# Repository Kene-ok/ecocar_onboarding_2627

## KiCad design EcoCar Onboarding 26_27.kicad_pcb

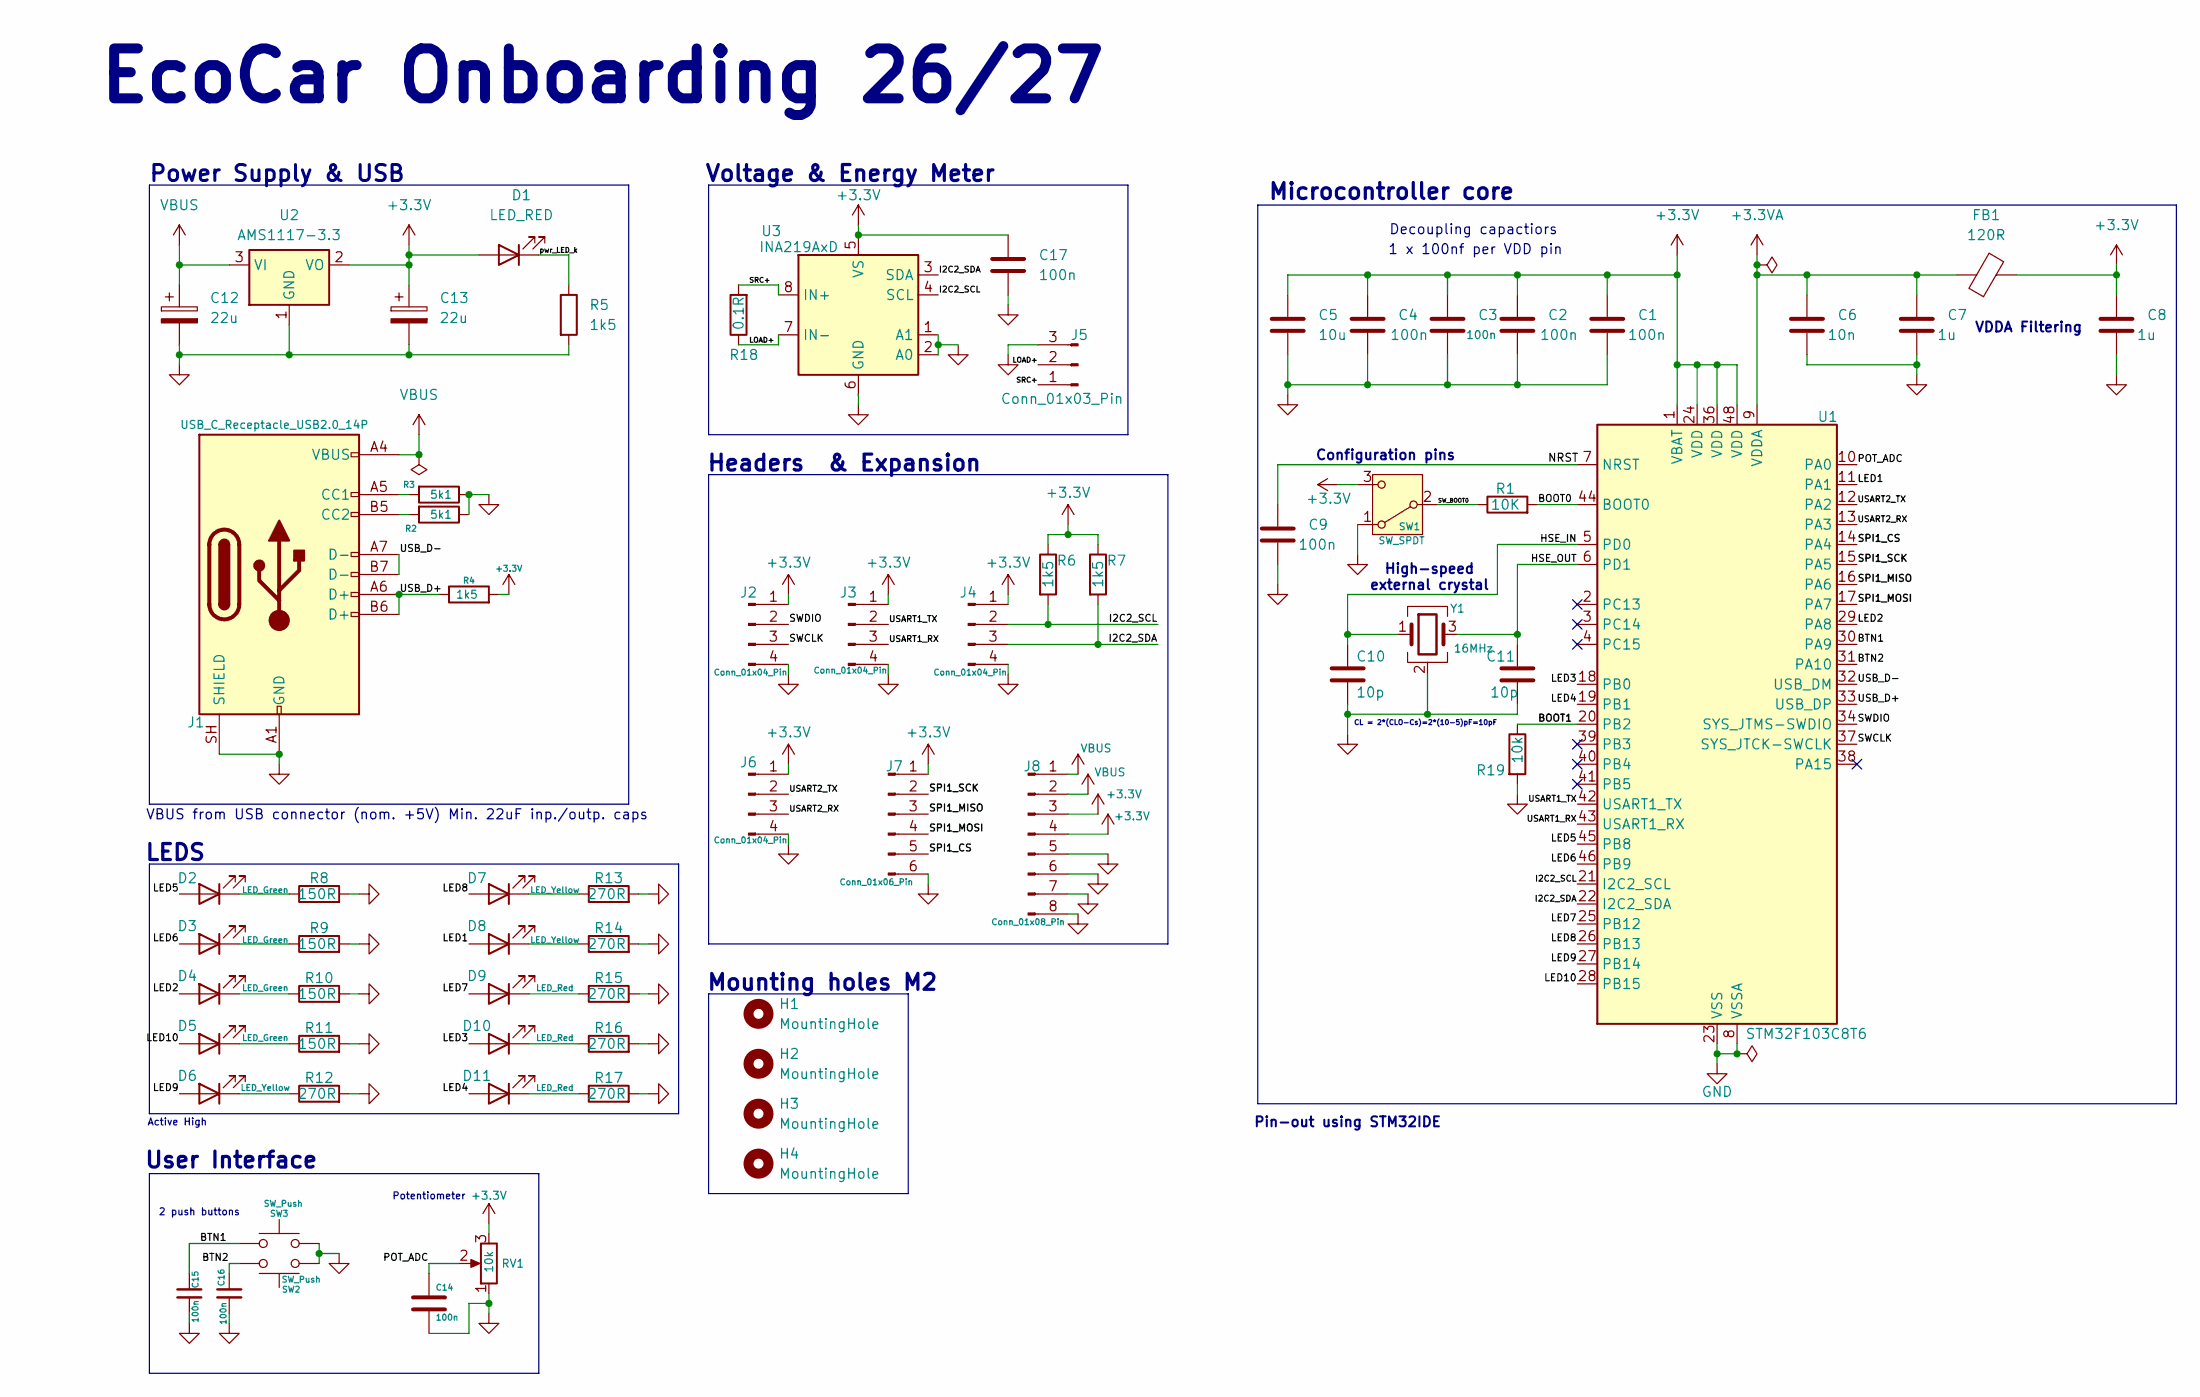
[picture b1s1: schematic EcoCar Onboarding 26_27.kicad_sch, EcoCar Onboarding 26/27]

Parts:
C1, C2, C3, C4, C9, C14, C15, C16, C17: 100n; C_0603_1608Metric_Pad1.08x0.95mm_HandSolder
C5: 10u; C_0603_1608Metric_Pad1.08x0.95mm_HandSolder
C6: 10n; C_0603_1608Metric_Pad1.08x0.95mm_HandSolder
C7, C8: 1u; C_0603_1608Metric_Pad1.08x0.95mm_HandSolder
C10, C11: 10p; C_0603_1608Metric_Pad1.08x0.95mm_HandSolder
C12, C13: 22u; CP_EIA-3216-18_Kemet-A
D1: LED_RED; LED_0603_1608Metric_Pad1.05x0.95mm_HandSolder
D2, D3, D4, D5: LED_Green; LED_0603_1608Metric_Pad1.05x0.95mm_HandSolder
D6, D7, D8: LED_Yellow; LED_0603_1608Metric_Pad1.05x0.95mm_HandSolder
D9, D10, D11: LED_Red; LED_0603_1608Metric_Pad1.05x0.95mm_HandSolder
FB1: 120R; L_0603_1608Metric_Pad1.05x0.95mm_HandSolder
H1, H2, H3, H4: MountingHole; MountingHole_2.2mm_M2_DIN965
J1: USB_C_Receptacle_USB2.0_14P; USB_C_Receptacle_HRO_TYPE-C-31-M-12
J2, J3, J4, J6: Conn_01x04_Pin; PinHeader_1x04_P2.54mm_Vertical
J5: Conn_01x03_Pin; PinHeader_1x03_P2.54mm_Vertical
J7: Conn_01x06_Pin; PinHeader_1x06_P2.54mm_Vertical
J8: Conn_01x08_Pin; PinHeader_1x08_P2.54mm_Vertical
R1: 10K; R_0603_1608Metric_Pad0.98x0.95mm_HandSolder
R2, R3: 5k1; R_0603_1608Metric_Pad0.98x0.95mm_HandSolder
R4, R5, R6, R7: 1k5; R_0603_1608Metric_Pad0.98x0.95mm_HandSolder
R8, R9, R10, R11: 150R; R_0603_1608Metric_Pad0.98x0.95mm_HandSolder
R12, R13, R14, R15, R16, R17: 270R; R_0603_1608Metric_Pad0.98x0.95mm_HandSolder
R18: 0.1R; R_1206_3216Metric_Pad1.30x1.75mm_HandSolder
R19: 10k; R_0603_1608Metric_Pad0.98x0.95mm_HandSolder
RV1: 10k; Potentiometer_Alpha_RD901F-40-00D_Single_Vertical
SW1: SW_SPDT; SW_Slide_SPDT_Straight_CK_OS102011MS2Q
SW2, SW3: SW_Push; SW_PUSH_6mm
U1: STM32F103C8T6; LQFP-48_7x7mm_P0.5mm
U2: AMS1117-3.3; SOT-223-3_TabPin2
U3: INA219AxD; SOIC-8_3.9x4.9mm_P1.27mm
Y1: 16MHz; Crystal_SMD_3225-4Pin_3.2x2.5mm_HandSoldering

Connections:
+3.3V: C1.1, C2.1, C3.1, C4.1, C5.1, C8.1, C13.1, C17.1, D1.2 (A), FB1.2, J2.1, J3.1, J4.1, J6.1, J7.1, J8.3, J8.4, R4.2, R6.1, R7.1, RV1.3, SW1.3 (C), U1.1 (VBAT), U1.24 (VDD), U1.36 (VDD), U1.48 (VDD), U2.2 (VO), U3.5 (VS)
+3.3VA: C6.1, C7.1, FB1.1, U1.9 (VDDA)
/BOOT0: R1.2, U1.44 (BOOT0)
/BOOT1: R19.1, U1.20 (PB2)
/BTN1: C15.1, SW3.1, U1.30 (PA9)
/BTN2: C16.1, SW2.2, U1.31 (PA10)
/HSE_IN: C10.1, U1.5 (PD0), Y1.1
/HSE_OUT: C11.1, U1.6 (PD1), Y1.3
/I2C2_SCL: J4.2, R6.2, U1.21 (I2C2_SCL), U3.4 (SCL)
/I2C2_SDA: J4.3, R7.2, U1.22 (I2C2_SDA), U3.3 (SDA)
/LED1: D8.2 (A), U1.11 (PA1)
/LED2: D4.2 (A), U1.29 (PA8)
/LED3: D10.2 (A), U1.18 (PB0)
/LED4: D11.2 (A), U1.19 (PB1)
/LED5: D2.2 (A), U1.45 (PB8)
/LED6: D3.2 (A), U1.46 (PB9)
/LED7: D9.2 (A), U1.25 (PB12)
/LED8: D7.2 (A), U1.26 (PB13)
/LED9: D6.2 (A), U1.27 (PB14)
/LED10: D5.2 (A), U1.28 (PB15)
/LOAD+: J5.2, R18.1, U3.7 (IN-)
/NRST: C9.1, U1.7 (NRST)
/POT_ADC: C14.1, RV1.2, U1.10 (PA0)
/SPI1_CS: J7.5, U1.14 (PA4)
/SPI1_MISO: J7.3, U1.16 (PA6)
/SPI1_MOSI: J7.4, U1.17 (PA7)
/SPI1_SCK: J7.2, U1.15 (PA5)
/SRC+: J5.1, R18.2, U3.8 (IN+)
/SWCLK: J2.3, U1.37 (SYS_JTCK-SWCLK)
/SWDIO: J2.2, U1.34 (SYS_JTMS-SWDIO)
/SW_BOOT0: R1.1, SW1.2 (B)
/USART1_RX: J3.3, U1.43 (USART1_RX)
/USART1_TX: J3.2, U1.42 (USART1_TX)
/USART2_RX: J6.3, U1.13 (PA3)
/USART2_TX: J6.2, U1.12 (PA2)
/USB_D+: J1.A6 (D+), J1.B6 (D+), R4.1, U1.33 (USB_DP)
/USB_D-: J1.A7 (D-), J1.B7 (D-), U1.32 (USB_DM)
/pwr_LED_k: D1.1 (K), R5.1
GND: C1.2, C2.2, C3.2, C4.2, C5.2, C6.2, C7.2, C8.2, C9.2, C10.2, C11.2, C12.2, C13.2, C14.2, C15.2, C16.2, C17.2, J1.A1 (GND), J1.A12 (GND), J1.B1 (GND), J1.B12 (GND), J1.SH (SHIELD), J2.4, J3.4, J4.4, J5.3, J6.4, J7.6, J8.5, J8.6, J8.7, J8.8, R2.1, R3.1, R5.2, R8.2, R9.2, R10.2, R11.2, R12.2, R13.2, R14.2, R15.2, R16.2, R17.2, R19.2, RV1.1, SW1.1 (A), SW2.1, SW3.2, U1.8 (VSSA), U1.23 (VSS), U1.35 (VSS), U1.47 (VSS), U2.1 (GND), U3.1 (A1), U3.2 (A0), U3.6 (GND), Y1.2 (G), Y1.4 (G)
unnamed: D2.1 (K), R8.1
unnamed: D3.1 (K), R9.1
unnamed: D4.1 (K), R10.1
unnamed: D5.1 (K), R11.1
unnamed: D6.1 (K), R12.1
unnamed: D7.1 (K), R13.1
unnamed: D8.1 (K), R14.1
unnamed: D9.1 (K), R15.1
unnamed: D10.1 (K), R16.1
unnamed: D11.1 (K), R17.1
unnamed: J1.A5 (CC1), R3.2
unnamed: J1.B5 (CC2), R2.2
VBUS: C12.1, J1.A4 (VBUS), J1.A9 (VBUS), J1.B4 (VBUS), J1.B9 (VBUS), J8.1, J8.2, U2.3 (VI)

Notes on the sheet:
Active High
VBUS from USB connector (nom. +5V) Min. 22uF inp./outp. caps
Power Supply & USB
Voltage & Energy Meter
Pin-out using STM32IDE
CL = 2*(CLO-Cs)=2*(10-5)pF=10pF
High-speed external crystal
Potentiometer
EcoCar Onboarding 26/27
Headers & Expansion
Decoupling capactiors
1 x 100nf per VDD pin
Configuration pins
2 push buttons
VDDA Filtering
LEDS
User Interface
Microcontroller core
Mounting holes M2

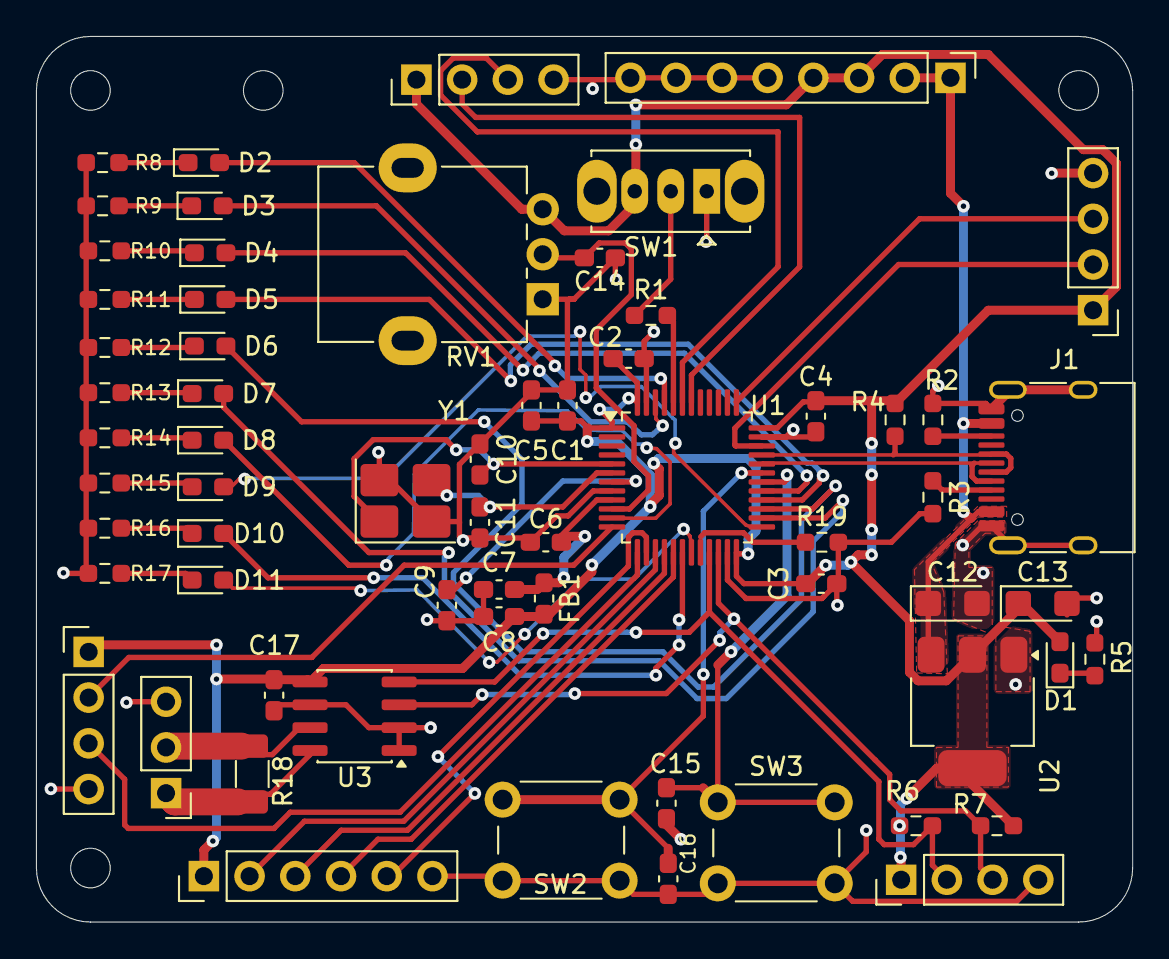
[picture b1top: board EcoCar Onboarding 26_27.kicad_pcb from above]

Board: 2 copper layers, 60.9 x 49.2 mm, 68 parts (0 on the bottom side), 52 nets.

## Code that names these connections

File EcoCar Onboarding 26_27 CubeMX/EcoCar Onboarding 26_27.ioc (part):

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Mcu.Name=STM32F103C(8-B)Tx
Mcu.Package=LQFP48
Mcu.UserName=STM32F103C8Tx
PA0-WKUP.Signal=ADCx_IN0
PA1.Signal=S_TIM2_CH2
PA10.GPIOParameters=GPIO_PuPd
PA10.GPIO_PuPd=GPIO_PULLUP
PA10.Signal=GPIO_Input
PA11.Mode=Device
PA11.Signal=USB_DM
PA12.Mode=Device
PA12.Signal=USB_DP
PA13.Mode=Serial_Wire
PA13.Signal=SYS_JTMS-SWDIO
PA14.Mode=Serial_Wire
PA14.Signal=SYS_JTCK-SWCLK
PA2.Mode=Asynchronous
PA2.Signal=USART2_TX
PA3.Mode=Asynchronous
PA3.Signal=USART2_RX
PA4.GPIOParameters=PinState,GPIO_Label
PA4.GPIO_Label=SPI1_CS
PA4.PinState=GPIO_PIN_SET
PA4.Signal=GPIO_Output
PA5.Mode=Full_Duplex_Master
PA5.Signal=SPI1_SCK
PA6.Mode=Full_Duplex_Master
PA6.Signal=SPI1_MISO
PA7.Mode=Full_Duplex_Master
PA7.Signal=SPI1_MOSI
PA8.Signal=S_TIM1_CH1
PA9.GPIOParameters=GPIO_PuPd
PA9.GPIO_PuPd=GPIO_PULLUP
PA9.Signal=GPIO_Input
PB0.Signal=S_TIM3_CH3
PB1.Signal=S_TIM3_CH4
PB10.Mode=I2C
PB10.Signal=I2C2_SCL
PB11.Mode=I2C
PB11.Signal=I2C2_SDA
PB12.Signal=GPIO_Output
PB13.Signal=GPIO_Output
PB14.Signal=GPIO_Output
PB15.Signal=GPIO_Output
PB6.Mode=Asynchronous
PB6.Signal=USART1_TX
PB7.Mode=Asynchronous
PB7.Signal=USART1_RX
PB8.Signal=S_TIM4_CH3
PB9.Signal=S_TIM4_CH4
PD0-OSC_IN.Mode=HSE-External-Oscillator
PD0-OSC_IN.Signal=RCC_OSC_IN
PD1-OSC_OUT.Mode=HSE-External-Oscillator
PD1-OSC_OUT.Signal=RCC_OSC_OUT
RCC.HSEDivPLL=RCC_HSE_PREDIV_DIV2
RCC.HSE_VALUE=16000000
RCC.SYSCLKFreq_VALUE=72000000
RCC.SYSCLKSource=RCC_SYSCLKSOURCE_PLLCLK
board=custom
